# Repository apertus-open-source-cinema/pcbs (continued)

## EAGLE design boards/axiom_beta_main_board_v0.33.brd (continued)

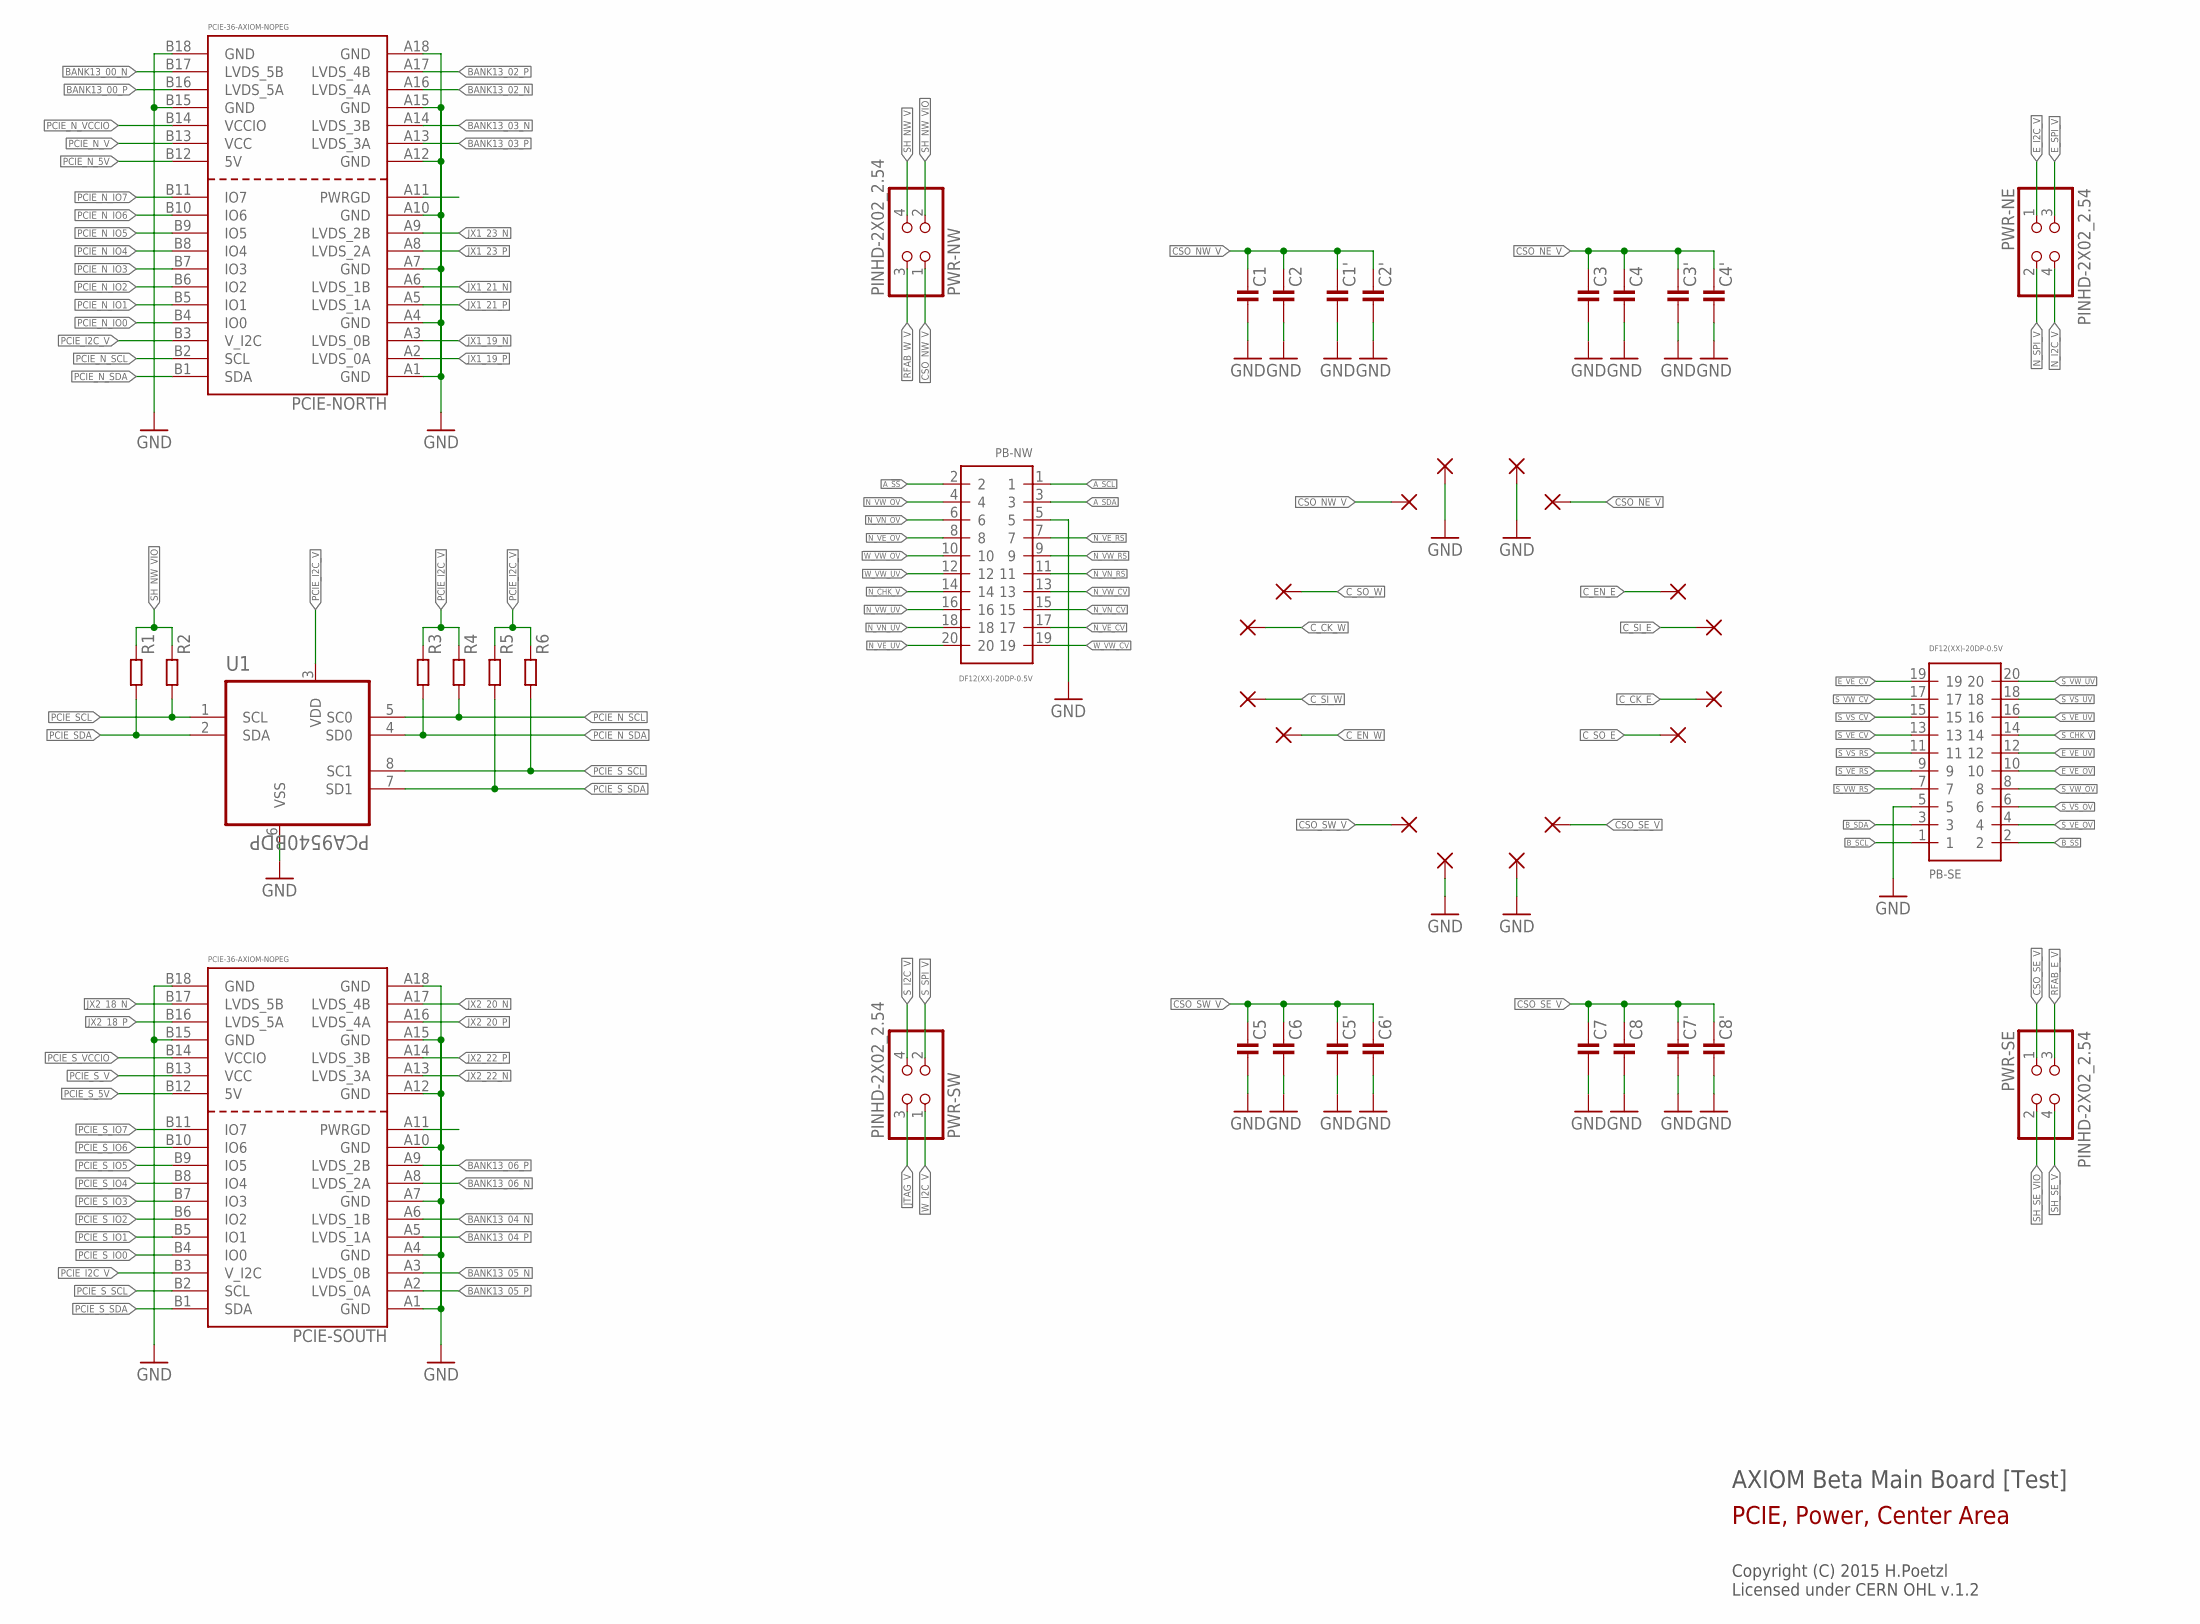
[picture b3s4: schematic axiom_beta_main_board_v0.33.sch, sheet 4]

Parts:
C1, C1', C3, C3', C5, C5', C7, C7': C0805-A; 0805-A
C2, C2', C4, C4', C6, C6', C8, C8': C0603-A; 0603-A
PB-NW: DF12(XX)-20DP-0.5V
PB-SE: DF12(XX)-20DP-0.5V
PCIE-NORTH: PCIE-36-AXIOM-NOPEG; PCIE-36-NOPEG
PCIE-SOUTH: PCIE-36-AXIOM-NOPEG; PCIE-36-NOPEG
PWR-NE: PINHD-2X02_2.54; 2X02
PWR-NW: PINHD-2X02_2.54; 2X02
PWR-SE: PINHD-2X02_2.54; 2X02
PWR-SW: PINHD-2X02_2.54; 2X02
R1, R2, R3, R4, R5, R6: R0402-B; 0402-B
U1: PCA9540BDP; SOP65P490X300-8N
U$1, U$2, U$3, U$4, U$5, U$6, U$11, U$14, U$15, U$16, U$17, U$18, U$19, U$20, U$21, U$22: PINPAD1.27MM; 1.2/0.6

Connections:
A_!SS: PB-NW.2; also elsewhere on the board
A_SCL: PB-NW.1; also elsewhere on the board
A_SDA: PB-NW.3; also elsewhere on the board
BANK13_00_N: PCIE-NORTH.B17 (LVDS_5B); also elsewhere on the board
BANK13_00_P: PCIE-NORTH.B16 (LVDS_5A); also elsewhere on the board
BANK13_02_N: PCIE-NORTH.A16 (LVDS_4A); also elsewhere on the board
BANK13_02_P: PCIE-NORTH.A17 (LVDS_4B); also elsewhere on the board
BANK13_03_N: PCIE-NORTH.A14 (LVDS_3B); also elsewhere on the board
BANK13_03_P: PCIE-NORTH.A13 (LVDS_3A); also elsewhere on the board
BANK13_04_N: PCIE-SOUTH.A6 (LVDS_1B); also elsewhere on the board
BANK13_04_P: PCIE-SOUTH.A5 (LVDS_1A); also elsewhere on the board
BANK13_05_N: PCIE-SOUTH.A3 (LVDS_0B); also elsewhere on the board
BANK13_05_P: PCIE-SOUTH.A2 (LVDS_0A); also elsewhere on the board
BANK13_06_N: PCIE-SOUTH.A8 (LVDS_2A); also elsewhere on the board
BANK13_06_P: PCIE-SOUTH.A9 (LVDS_2B); also elsewhere on the board
B_!SS: PB-SE.2; also elsewhere on the board
B_SCL: PB-SE.1; also elsewhere on the board
B_SDA: PB-SE.3; also elsewhere on the board
CSO_NE_V: C3.1, C3'.1, C4.1, C4'.1, U$19.1; also elsewhere on the board
CSO_NW_V: C1.1, C1'.1, C2.1, C2'.1, PWR-NW.1, U$18.1
CSO_SE_V: C7.1, C7'.1, C8.1, C8'.1, PWR-SE.1, U$21.1
CSO_SW_V: C5.1, C5'.1, C6.1, C6'.1, U$22.1; also elsewhere on the board
C_CK_E: U$14.1; also elsewhere on the board
C_CK_W: U$1.1; also elsewhere on the board
C_EN_E: U$3.1; also elsewhere on the board
C_EN_W: U$4.1; also elsewhere on the board
C_SI_E: U$15.1; also elsewhere on the board
C_SI_W: U$2.1; also elsewhere on the board
C_SO_E: U$16.1; also elsewhere on the board
C_SO_W: U$11.1; also elsewhere on the board
E_I2C_V: PWR-NE.1; also elsewhere on the board
E_SPI_V: PWR-NE.3; also elsewhere on the board
E_VE_CV: PB-SE.19; also elsewhere on the board
E_VE_OV: PB-SE.10; also elsewhere on the board
E_VE_UV: PB-SE.12; also elsewhere on the board
GND: C1.2, C1'.2, C2.2, C2'.2, C3.2, C3'.2, C4.2, C4'.2, C5.2, C5'.2, C6.2, C6'.2, C7.2, C7'.2, C8.2, C8'.2, PB-NW.5, PB-SE.5, PCIE-NORTH.A1 (GND), PCIE-NORTH.A4 (GND), PCIE-NORTH.A7 (GND), PCIE-NORTH.A10 (GND), PCIE-NORTH.A12 (GND), PCIE-NORTH.A15 (GND), PCIE-NORTH.A18 (GND), PCIE-NORTH.B15 (GND), PCIE-NORTH.B18 (GND), PCIE-SOUTH.A1 (GND), PCIE-SOUTH.A4 (GND), PCIE-SOUTH.A7 (GND), PCIE-SOUTH.A10 (GND), PCIE-SOUTH.A12 (GND), PCIE-SOUTH.A15 (GND), PCIE-SOUTH.A18 (GND), PCIE-SOUTH.B15 (GND), PCIE-SOUTH.B18 (GND), U1.6 (VSS), U$5.1, U$6.1, U$17.1, U$20.1; also elsewhere on the board
JTAG_V: PWR-SW.3; also elsewhere on the board
JX1_19_N: PCIE-NORTH.A3 (LVDS_0B); also elsewhere on the board
JX1_19_P: PCIE-NORTH.A2 (LVDS_0A); also elsewhere on the board
JX1_21_N: PCIE-NORTH.A6 (LVDS_1B); also elsewhere on the board
JX1_21_P: PCIE-NORTH.A5 (LVDS_1A); also elsewhere on the board
JX1_23_N: PCIE-NORTH.A9 (LVDS_2B); also elsewhere on the board
JX1_23_P: PCIE-NORTH.A8 (LVDS_2A); also elsewhere on the board
JX2_18_N: PCIE-SOUTH.B17 (LVDS_5B); also elsewhere on the board
JX2_18_P: PCIE-SOUTH.B16 (LVDS_5A); also elsewhere on the board
JX2_20_N: PCIE-SOUTH.A17 (LVDS_4B); also elsewhere on the board
JX2_20_P: PCIE-SOUTH.A16 (LVDS_4A); also elsewhere on the board
JX2_22_N: PCIE-SOUTH.A13 (LVDS_3A); also elsewhere on the board
JX2_22_P: PCIE-SOUTH.A14 (LVDS_3B); also elsewhere on the board
N_CHK_V: PB-NW.14; also elsewhere on the board
N_I2C_V: PWR-NE.4; also elsewhere on the board
N_SPI_V: PWR-NE.2; also elsewhere on the board
N_VE_CV: PB-NW.17; also elsewhere on the board
N_VE_OV: PB-NW.8; also elsewhere on the board
N_VE_RS: PB-NW.7; also elsewhere on the board
N_VE_UV: PB-NW.20; also elsewhere on the board
N_VN_CV: PB-NW.15; also elsewhere on the board
N_VN_OV: PB-NW.6; also elsewhere on the board
N_VN_RS: PB-NW.11; also elsewhere on the board
N_VN_UV: PB-NW.18; also elsewhere on the board
N_VW_CV: PB-NW.13; also elsewhere on the board
N_VW_OV: PB-NW.4; also elsewhere on the board
N_VW_RS: PB-NW.9; also elsewhere on the board
N_VW_UV: PB-NW.16; also elsewhere on the board
PCIE_I2C_V: PCIE-NORTH.B3 (V_I2C), PCIE-SOUTH.B3 (V_I2C), R3.1, R4.1, R5.1, R6.1, U1.3 (VDD); also elsewhere on the board
PCIE_N_5V: PCIE-NORTH.B12 (5V); also elsewhere on the board
PCIE_N_IO0: PCIE-NORTH.B4 (IO0); also elsewhere on the board
PCIE_N_IO1: PCIE-NORTH.B5 (IO1); also elsewhere on the board
PCIE_N_IO2: PCIE-NORTH.B6 (IO2); also elsewhere on the board
PCIE_N_IO3: PCIE-NORTH.B7 (IO3); also elsewhere on the board
PCIE_N_IO4: PCIE-NORTH.B8 (IO4); also elsewhere on the board
PCIE_N_IO5: PCIE-NORTH.B9 (IO5); also elsewhere on the board
PCIE_N_IO6: PCIE-NORTH.B10 (IO6); also elsewhere on the board
PCIE_N_IO7: PCIE-NORTH.B11 (IO7); also elsewhere on the board
PCIE_N_SCL: PCIE-NORTH.B2 (SCL), R4.2, U1.5 (SC0)
PCIE_N_SDA: PCIE-NORTH.B1 (SDA), R3.2, U1.4 (SD0)
PCIE_N_V: PCIE-NORTH.B13 (VCC); also elsewhere on the board
PCIE_N_VCCIO: PCIE-NORTH.B14 (VCCIO); also elsewhere on the board
PCIE_SCL: R2.2, U1.1 (SCL); also elsewhere on the board
PCIE_SDA: R1.2, U1.2 (SDA); also elsewhere on the board
PCIE_S_5V: PCIE-SOUTH.B12 (5V); also elsewhere on the board
PCIE_S_IO0: PCIE-SOUTH.B4 (IO0); also elsewhere on the board
PCIE_S_IO1: PCIE-SOUTH.B5 (IO1); also elsewhere on the board
PCIE_S_IO2: PCIE-SOUTH.B6 (IO2); also elsewhere on the board
PCIE_S_IO3: PCIE-SOUTH.B7 (IO3); also elsewhere on the board
PCIE_S_IO4: PCIE-SOUTH.B8 (IO4); also elsewhere on the board
PCIE_S_IO5: PCIE-SOUTH.B9 (IO5); also elsewhere on the board
PCIE_S_IO6: PCIE-SOUTH.B10 (IO6); also elsewhere on the board
PCIE_S_IO7: PCIE-SOUTH.B11 (IO7); also elsewhere on the board
PCIE_S_SCL: PCIE-SOUTH.B2 (SCL), R6.2, U1.8 (SC1)
PCIE_S_SDA: PCIE-SOUTH.B1 (SDA), R5.2, U1.7 (SD1)
PCIE_S_V: PCIE-SOUTH.B13 (VCC); also elsewhere on the board
PCIE_S_VCCIO: PCIE-SOUTH.B14 (VCCIO); also elsewhere on the board
RFAB_E_V: PWR-SE.3; also elsewhere on the board
RFAB_W_V: PWR-NW.3; also elsewhere on the board
SH_NW_V: PWR-NW.4; also elsewhere on the board
SH_NW_VIO: PWR-NW.2, R1.1, R2.1; also elsewhere on the board
SH_SE_V: PWR-SE.4; also elsewhere on the board
SH_SE_VIO: PWR-SE.2; also elsewhere on the board
S_CHK_V: PB-SE.14; also elsewhere on the board
S_I2C_V: PWR-SW.4; also elsewhere on the board
S_SPI_V: PWR-SW.2; also elsewhere on the board
S_VE_CV: PB-SE.13; also elsewhere on the board
S_VE_OV: PB-SE.4; also elsewhere on the board
S_VE_RS: PB-SE.9; also elsewhere on the board
S_VE_UV: PB-SE.16; also elsewhere on the board
S_VS_CV: PB-SE.15; also elsewhere on the board
S_VS_OV: PB-SE.6; also elsewhere on the board
S_VS_RS: PB-SE.11; also elsewhere on the board
S_VS_UV: PB-SE.18; also elsewhere on the board
S_VW_CV: PB-SE.17; also elsewhere on the board
S_VW_OV: PB-SE.8; also elsewhere on the board
S_VW_RS: PB-SE.7; also elsewhere on the board
S_VW_UV: PB-SE.20; also elsewhere on the board
W_I2C_V: PWR-SW.1; also elsewhere on the board
W_VW_CV: PB-NW.19; also elsewhere on the board
W_VW_OV: PB-NW.10; also elsewhere on the board
W_VW_UV: PB-NW.12; also elsewhere on the board

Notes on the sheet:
AXIOM Beta Main Board [Test]
Copyright (C) 2015 H.Poetzl Licensed under CERN OHL v.1.2
PCIE, Power, Center Area

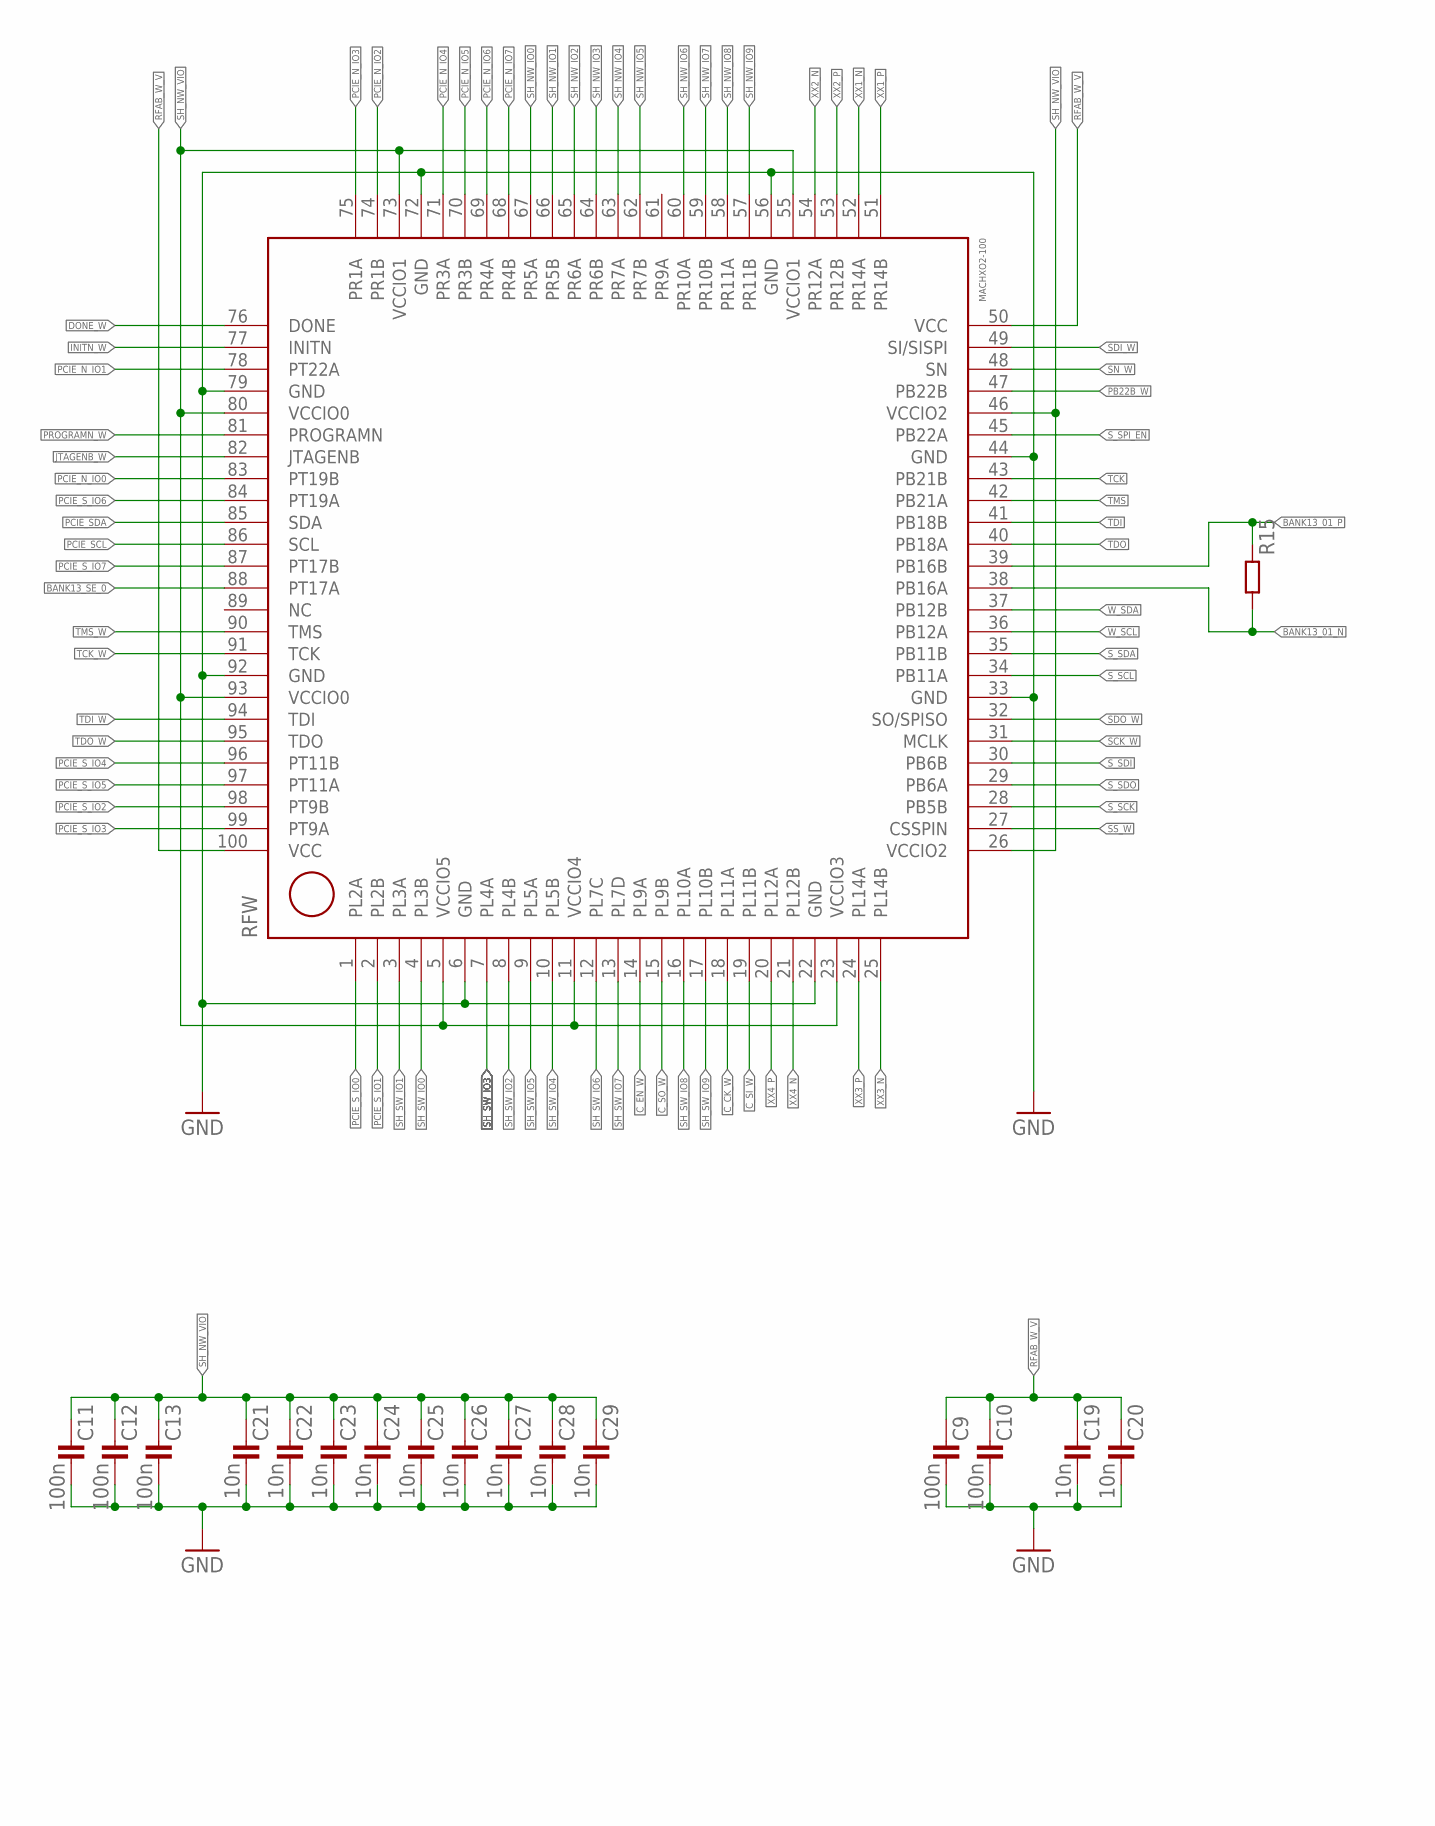
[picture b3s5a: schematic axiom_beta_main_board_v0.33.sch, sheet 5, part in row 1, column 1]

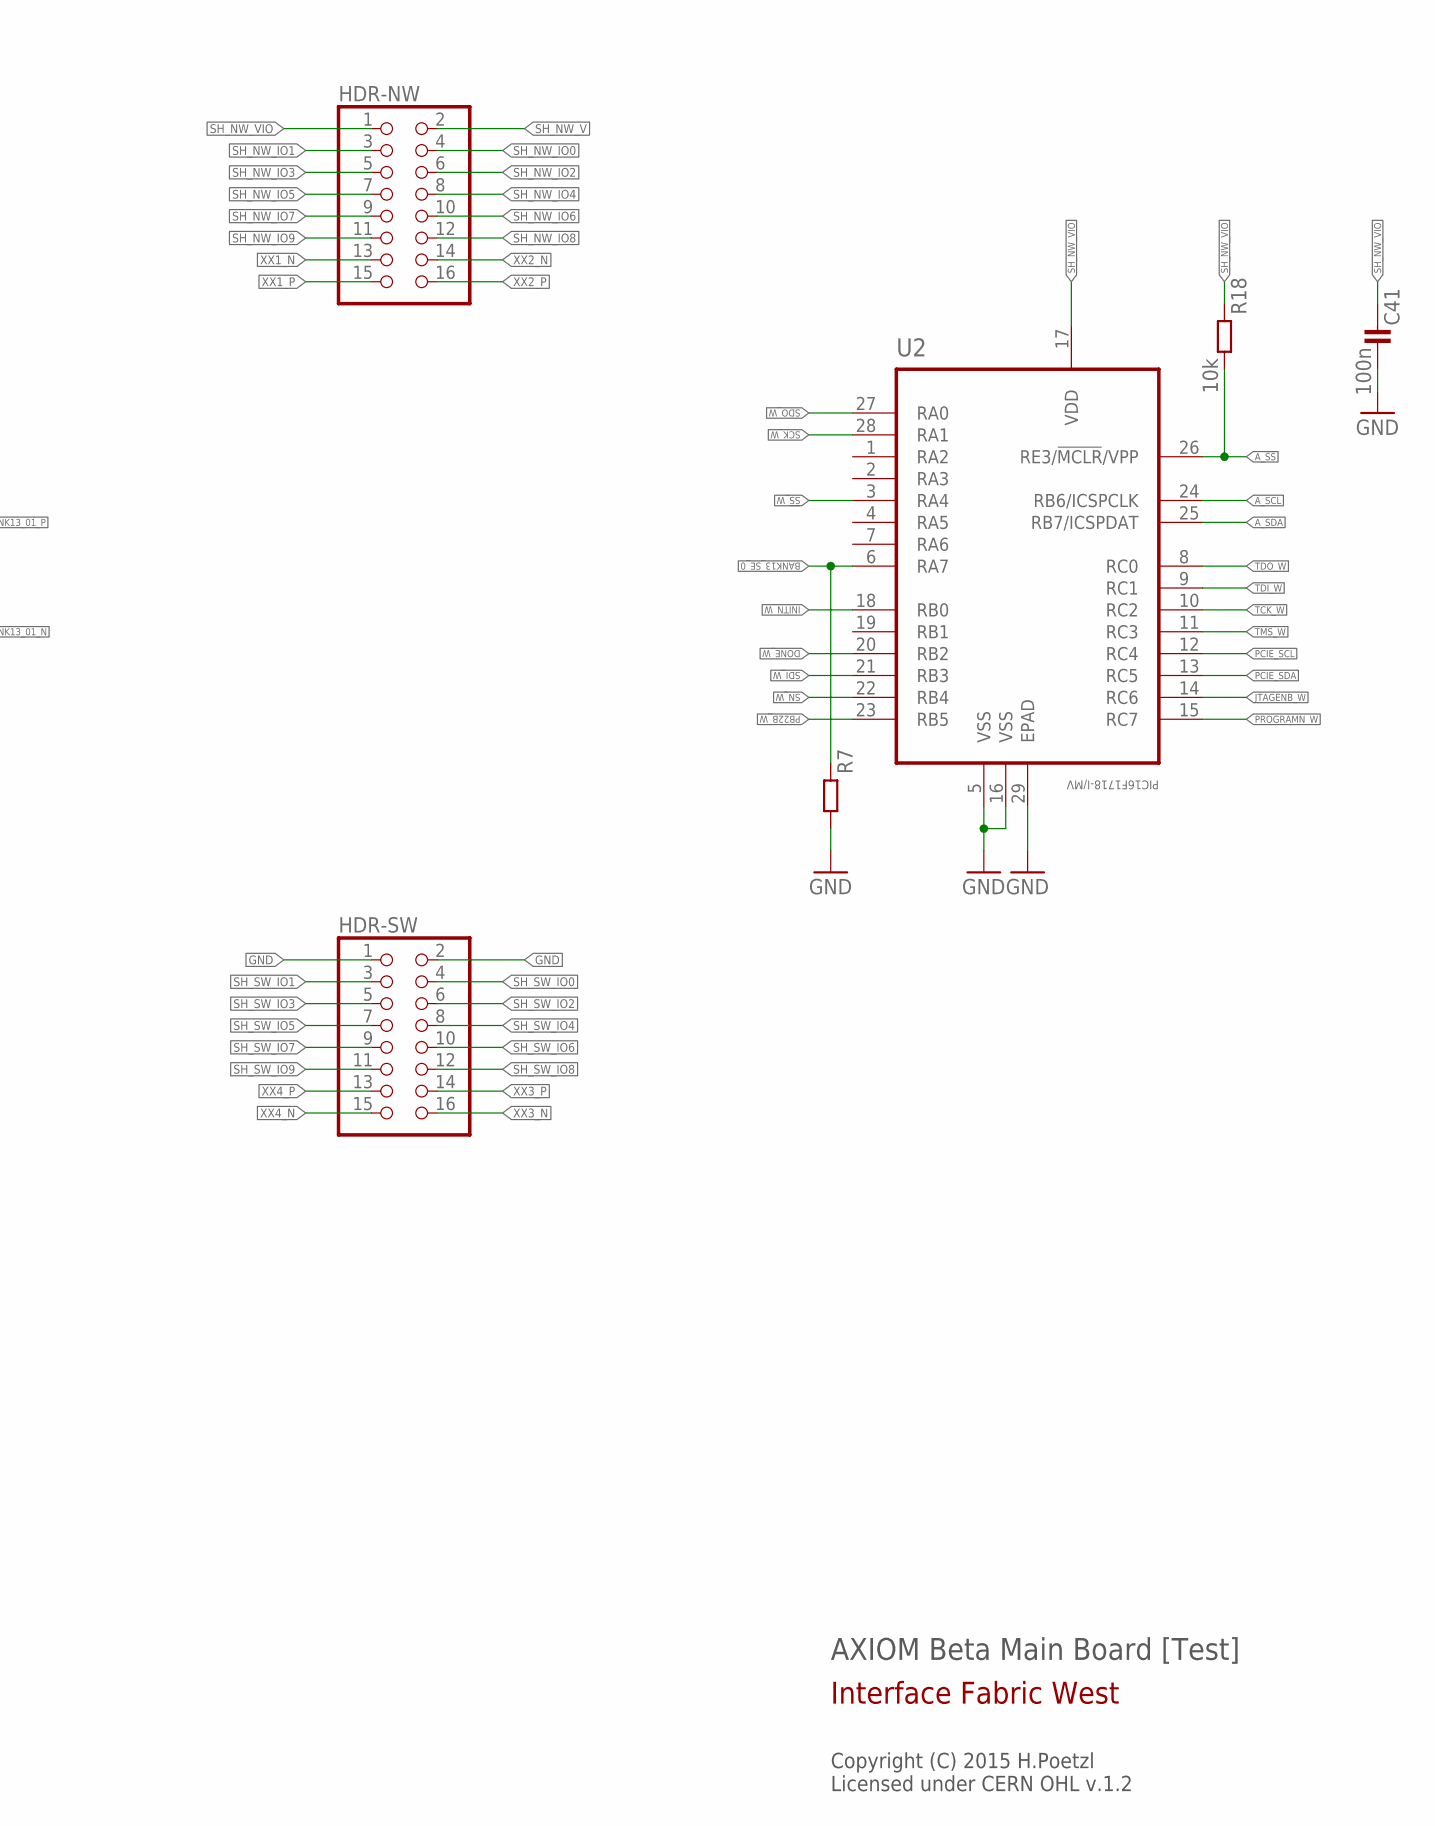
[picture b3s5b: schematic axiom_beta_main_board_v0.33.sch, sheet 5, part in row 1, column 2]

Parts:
C9, C10, C11, C12, C13, C41: 100n; 0402-B
C19, C20, C21, C22, C23, C24, C25, C26, C27, C28, C29: 10n; 0402-B
HDR-NW: PINHD-2X08_2.00_LPR; 62101621821
HDR-SW: PINHD-2X08_2.00_LPR; 62101621821
R7: R0402-B; 0402-B
R15: R0201-B; 0201-B
R18: 10k; 0402-B
RFW: MACHXO2-100; MACHXO2-100TQFP
U2: PIC16F1718-I/MV; QFN40P400X400X55-29N

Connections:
!SS!_W: RFW.27 (CSSPIN), U2.3 (RA4)
A_!SS: R18.2, U2.26 (RE3/!MCLR!/VPP); also elsewhere on the board
A_SCL: U2.24 (RB6/ICSPCLK); also elsewhere on the board
A_SDA: U2.25 (RB7/ICSPDAT); also elsewhere on the board
BANK13_01_N: R15.2, RFW.38 (PB16A); also elsewhere on the board
BANK13_01_P: R15.1, RFW.39 (PB16B); also elsewhere on the board
BANK13_SE_0: R7.1, RFW.88 (PT17A), U2.6 (RA7); also elsewhere on the board
C_CK_W: RFW.18 (PL11A); also elsewhere on the board
C_EN_W: RFW.14 (PL9A); also elsewhere on the board
C_SI_W: RFW.19 (PL11B); also elsewhere on the board
C_SO_W: RFW.15 (PL9B); also elsewhere on the board
DONE_W: RFW.76 (DONE), U2.20 (RB2)
GND: C9.2, C10.2, C11.2, C12.2, C13.2, C19.2, C20.2, C21.2, C22.2, C23.2, C24.2, C25.2, C26.2, C27.2, C28.2, C29.2, C41.2, HDR-SW.1, HDR-SW.2, R7.2, RFW.6 (GND), RFW.22 (GND), RFW.33 (GND), RFW.44 (GND), RFW.56 (GND), RFW.72 (GND), RFW.79 (GND), RFW.92 (GND), U2.5 (VSS), U2.16 (VSS), U2.29 (EPAD); also elsewhere on the board
INITN_W: RFW.77 (INITN), U2.18 (RB0)
JTAGENB_W: RFW.82 (JTAGENB), U2.14 (RC6)
PB22B_W: RFW.47 (PB22B), U2.23 (RB5)
PCIE_N_IO0: RFW.83 (PT19B); also elsewhere on the board
PCIE_N_IO1: RFW.78 (PT22A); also elsewhere on the board
PCIE_N_IO2: RFW.74 (PR1B); also elsewhere on the board
PCIE_N_IO3: RFW.75 (PR1A); also elsewhere on the board
PCIE_N_IO4: RFW.71 (PR3A); also elsewhere on the board
PCIE_N_IO5: RFW.70 (PR3B); also elsewhere on the board
PCIE_N_IO6: RFW.69 (PR4A); also elsewhere on the board
PCIE_N_IO7: RFW.68 (PR4B); also elsewhere on the board
PCIE_SCL: RFW.86 (SCL), U2.12 (RC4); also elsewhere on the board
PCIE_SDA: RFW.85 (SDA), U2.13 (RC5); also elsewhere on the board
PCIE_S_IO0: RFW.1 (PL2A); also elsewhere on the board
PCIE_S_IO1: RFW.2 (PL2B); also elsewhere on the board
PCIE_S_IO2: RFW.98 (PT9B); also elsewhere on the board
PCIE_S_IO3: RFW.99 (PT9A); also elsewhere on the board
PCIE_S_IO4: RFW.96 (PT11B); also elsewhere on the board
PCIE_S_IO5: RFW.97 (PT11A); also elsewhere on the board
PCIE_S_IO6: RFW.84 (PT19A); also elsewhere on the board
PCIE_S_IO7: RFW.87 (PT17B); also elsewhere on the board
PROGRAMN_W: RFW.81 (PROGRAMN), U2.15 (RC7)
RFAB_W_V: C9.1, C10.1, C19.1, C20.1, RFW.50 (VCC), RFW.100 (VCC); also elsewhere on the board
SCK_W: RFW.31 (MCLK), U2.28 (RA1)
SDI_W: RFW.49 (SI/SISPI), U2.21 (RB3)
SDO_W: RFW.32 (SO/SPISO), U2.27 (RA0)
SH_NW_IO0: HDR-NW.4, RFW.67 (PR5A)
SH_NW_IO1: HDR-NW.3, RFW.66 (PR5B)
SH_NW_IO2: HDR-NW.6, RFW.65 (PR6A)
SH_NW_IO3: HDR-NW.5, RFW.64 (PR6B)
SH_NW_IO4: HDR-NW.8, RFW.63 (PR7A)
SH_NW_IO5: HDR-NW.7, RFW.62 (PR7B)
SH_NW_IO6: HDR-NW.10, RFW.60 (PR10A)
SH_NW_IO7: HDR-NW.9, RFW.59 (PR10B)
SH_NW_IO8: HDR-NW.12, RFW.58 (PR11A)
SH_NW_IO9: HDR-NW.11, RFW.57 (PR11B)
SH_NW_V: HDR-NW.2; also elsewhere on the board
SH_NW_VIO: C11.1, C12.1, C13.1, C21.1, C22.1, C23.1, C24.1, C25.1, C26.1, C27.1, C28.1, C29.1, C41.1, HDR-NW.1, R18.1, RFW.5 (VCCIO5), RFW.11 (VCCIO4), RFW.23 (VCCIO3), RFW.26 (VCCIO2), RFW.46 (VCCIO2), RFW.55 (VCCIO1), RFW.73 (VCCIO1), RFW.80 (VCCIO0), RFW.93 (VCCIO0), U2.17 (VDD); also elsewhere on the board
SH_SW_IO0: HDR-SW.4, RFW.4 (PL3B)
SH_SW_IO1: HDR-SW.3, RFW.3 (PL3A)
SH_SW_IO2: HDR-SW.6, RFW.8 (PL4B)
SH_SW_IO3: HDR-SW.5, RFW.7 (PL4A)
SH_SW_IO4: HDR-SW.8, RFW.10 (PL5B)
SH_SW_IO5: HDR-SW.7, RFW.9 (PL5A)
SH_SW_IO6: HDR-SW.10, RFW.12 (PL7C)
SH_SW_IO7: HDR-SW.9, RFW.13 (PL7D)
SH_SW_IO8: HDR-SW.12, RFW.16 (PL10A)
SH_SW_IO9: HDR-SW.11, RFW.17 (PL10B)
SN_W: RFW.48 (SN), U2.22 (RB4)
S_SCK: RFW.28 (PB5B); also elsewhere on the board
S_SCL: RFW.34 (PB11A); also elsewhere on the board
S_SDA: RFW.35 (PB11B); also elsewhere on the board
S_SDI: RFW.30 (PB6B); also elsewhere on the board
S_SDO: RFW.29 (PB6A); also elsewhere on the board
S_SPI_EN: RFW.45 (PB22A); also elsewhere on the board
TCK: RFW.43 (PB21B); also elsewhere on the board
TCK_W: RFW.91 (TCK), U2.10 (RC2)
TDI: RFW.41 (PB18B); also elsewhere on the board
TDI_W: RFW.94 (TDI), U2.9 (RC1)
TDO: RFW.40 (PB18A); also elsewhere on the board
TDO_W: RFW.95 (TDO), U2.8 (RC0)
TMS: RFW.42 (PB21A); also elsewhere on the board
TMS_W: RFW.90 (TMS), U2.11 (RC3)
W_SCL: RFW.36 (PB12A); also elsewhere on the board
W_SDA: RFW.37 (PB12B); also elsewhere on the board
XX1_N: HDR-NW.13, RFW.52 (PR14A)
XX1_P: HDR-NW.15, RFW.51 (PR14B)
XX2_N: HDR-NW.14, RFW.54 (PR12A)
XX2_P: HDR-NW.16, RFW.53 (PR12B)
XX3_N: HDR-SW.16, RFW.25 (PL14B)
XX3_P: HDR-SW.14, RFW.24 (PL14A)
XX4_N: HDR-SW.15, RFW.21 (PL12B)
XX4_P: HDR-SW.13, RFW.20 (PL12A)

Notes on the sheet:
AXIOM Beta Main Board [Test]
Copyright (C) 2015 H.Poetzl Licensed under CERN OHL v.1.2
Interface Fabric West
